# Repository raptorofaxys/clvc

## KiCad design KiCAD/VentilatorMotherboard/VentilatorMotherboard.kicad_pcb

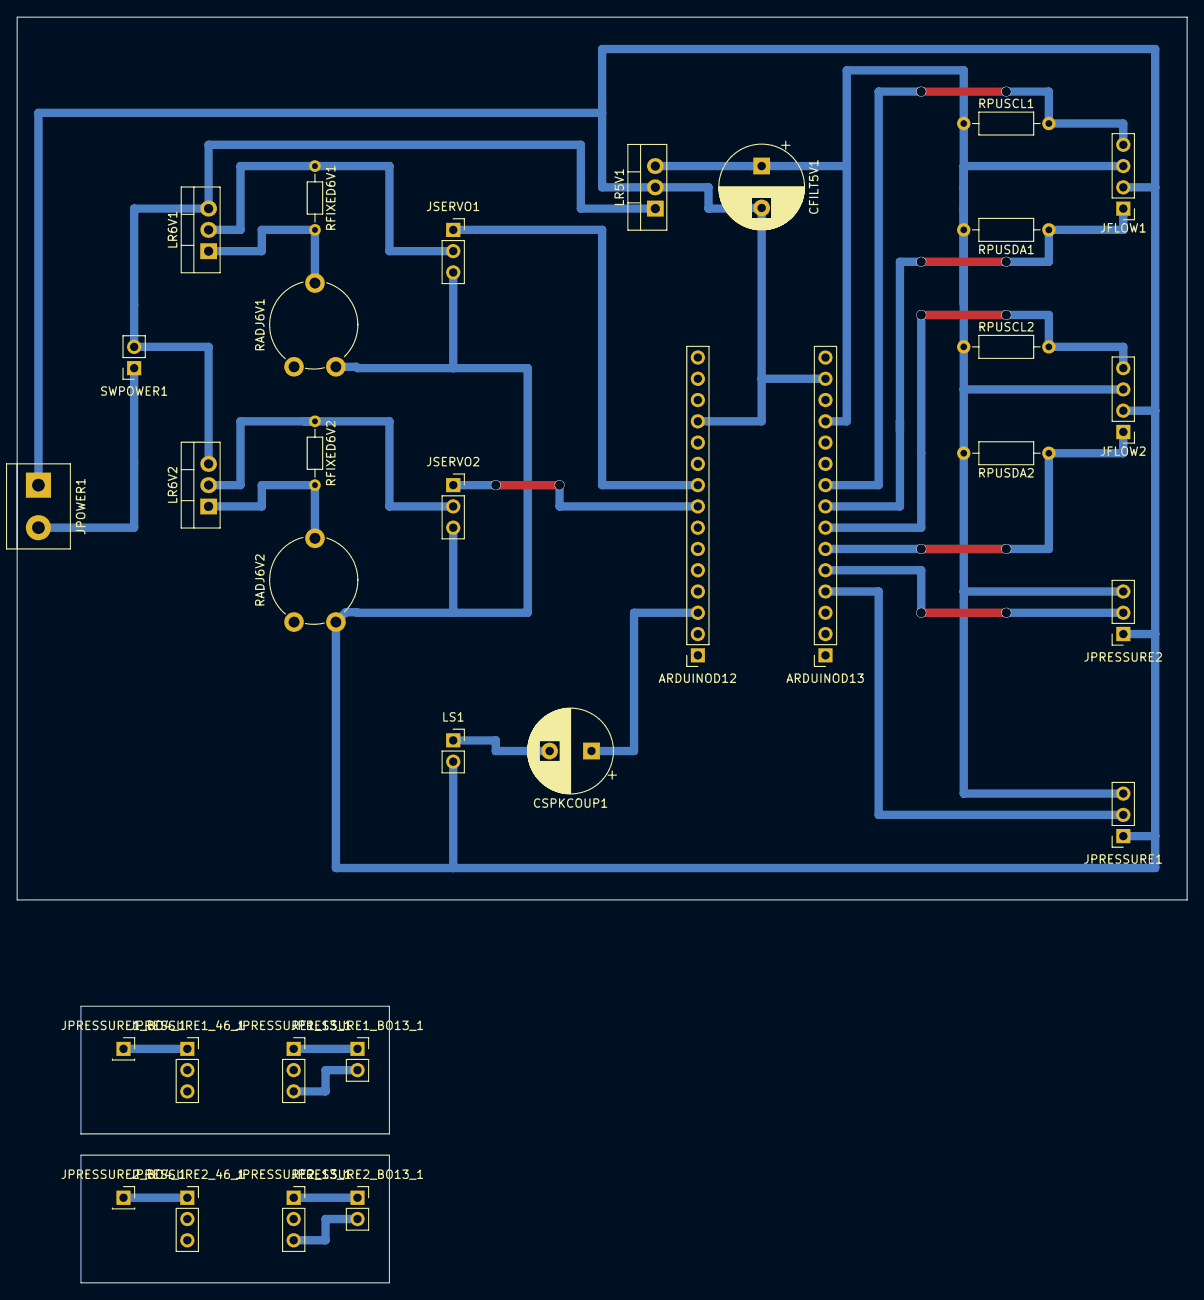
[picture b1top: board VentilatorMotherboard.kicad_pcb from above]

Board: 2 copper layers, 139.7 x 151.1 mm, 32 parts (0 on the bottom side), 24 nets.

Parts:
ARDUINOD12, ARDUINOD13: Conn_01x15_Female; PinSocket_1x15_P2.54mm_Vertical
CFILT5V1: 2200u; CP_Radial_D10.0mm_P5.00mm
CSPKCOUP1: 220u; CP_Radial_D10.0mm_P5.00mm
JFLOW1, JFLOW2: Conn_01x04_Male; PinHeader_1x04_P2.54mm_Vertical
JPOWER1: Conn_01x02_Female; TerminalBlock_bornier-2_P5.08mm
JPRESSURE1, JPRESSURE1_13_1, JPRESSURE1_46_1, JPRESSURE2, JPRESSURE2_13_1, JPRESSURE2_46_1: Conn_01x03_Male; PinSocket_1x03_P2.54mm_Vertical
JPRESSURE1_BO4_1, JPRESSURE2_BO4_1: Conn_01x01_Male; PinSocket_1x01_P2.54mm_Vertical
JPRESSURE1_BO13_1, JPRESSURE2_BO13_1: Conn_01x02_Male; PinSocket_1x02_P2.54mm_Vertical
JSERVO1, JSERVO2: Conn_01x03_Male; PinSocket_1x03_P2.54mm_Vertical
LR5V1: L7805; TO-220-3_Vertical
LR6V1, LR6V2: LM317_3PinPackage; TO-220-3_Vertical
LS1: Speaker; PinSocket_1x02_P2.54mm_Vertical
RADJ6V1, RADJ6V2: R_POT_TRIM; Potentiometer_Piher_PT-10-V10_Vertical
RFIXED6V1, RFIXED6V2: 220; R_Axial_DIN0204_L3.6mm_D1.6mm_P7.62mm_Horizontal
RPUSCL1, RPUSCL2: 4K7; R_Axial_DIN0207_L6.3mm_D2.5mm_P10.16mm_Horizontal
RPUSDA1, RPUSDA2: 4K7; R_Axial_DIN0207_L6.3mm_D2.5mm_P10.16mm_Horizontal
SWPOWER1: SW_SPST; PinSocket_1x02_P2.54mm_Vertical

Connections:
+5V: ARDUINOD13.12, CFILT5V1.1, JFLOW1.3, JFLOW2.3, JPRESSURE1.3, JPRESSURE2.3, LR5V1.3, RPUSCL1.1, RPUSCL2.1, RPUSDA1.2, RPUSDA2.2
/6V1: JSERVO1.2, LR6V1.2, RFIXED6V1.1
/6V2: JSERVO2.2, LR6V2.2, RFIXED6V2.1
/A0: ARDUINOD13.4, JPRESSURE1.2
/A1: ARDUINOD13.5, JPRESSURE2.2
/A2: ARDUINOD13.6, JFLOW2.1, RPUSDA2.1
/A3: ARDUINOD13.7, JFLOW2.4, RPUSCL2.2
/A4: ARDUINOD13.8, JFLOW1.1, RPUSDA1.1
/A5: ARDUINOD13.9, JFLOW1.4, RPUSCL1.2
/D4: ARDUINOD12.9, JSERVO1.1
/D5: ARDUINOD12.8, JSERVO2.1
/D10: ARDUINOD12.3, CSPKCOUP1.1
GND: ARDUINOD12.12, ARDUINOD13.14, CFILT5V1.2, JFLOW1.2, JFLOW2.2, JPOWER1.1, JPRESSURE1.1, JPRESSURE2.1, JSERVO1.3, JSERVO2.3, LR5V1.2, LS1.2, RADJ6V1.1, RADJ6V2.1
unnamed: CSPKCOUP1.2, LS1.1
unnamed: JPOWER1.2, SWPOWER1.1
unnamed: JPRESSURE1_13_1.1, JPRESSURE1_BO13_1.1
unnamed: JPRESSURE1_13_1.3, JPRESSURE1_BO13_1.2
unnamed: JPRESSURE1_46_1.1, JPRESSURE1_BO4_1.1
unnamed: JPRESSURE2_13_1.1, JPRESSURE2_BO13_1.1
unnamed: JPRESSURE2_13_1.3, JPRESSURE2_BO13_1.2
unnamed: JPRESSURE2_46_1.1, JPRESSURE2_BO4_1.1
unnamed: LR5V1.1, LR6V1.3, LR6V2.3, SWPOWER1.2
unnamed: LR6V1.1, RADJ6V1.2, RFIXED6V1.2
unnamed: LR6V2.1, RADJ6V2.2, RFIXED6V2.2

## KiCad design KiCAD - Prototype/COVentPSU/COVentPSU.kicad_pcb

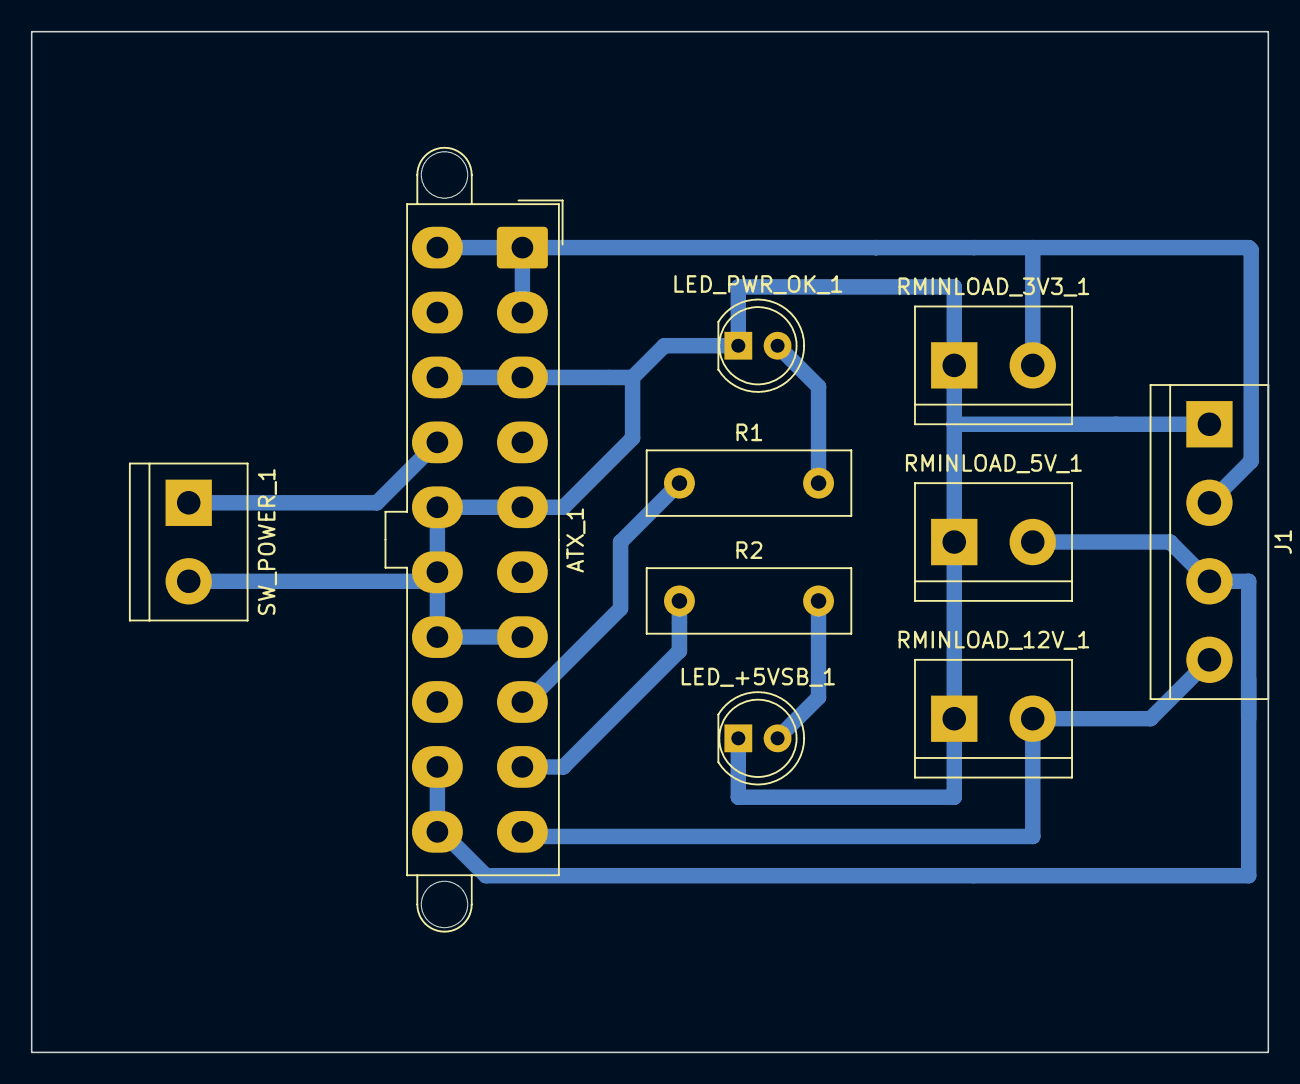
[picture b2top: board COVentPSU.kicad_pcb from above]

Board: 2 copper layers, 80.0 x 66.0 mm, 10 parts (0 on the bottom side), 9 nets.

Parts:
ATX_1: Conn_02x10_Top_Bottom; Molex_Mini-Fit_Jr_5566-20A2_2x10_P4.20mm_Vertical
J1: Conn_01x04_Female; TerminalBlock_bornier-4_P5.08mm
LED_+5VSB_1: LED_+5VSB; LED_D5.0mm
LED_PWR_OK_1: LED_PWR_OK; LED_D5.0mm
R1, R2: 300; R_Box_L13.0mm_W4.0mm_P9.00mm
RMINLOAD_3V3_1: 5; TerminalBlock_bornier-2_P5.08mm
RMINLOAD_5V_1, RMINLOAD_12V_1: 10; TerminalBlock_bornier-2_P5.08mm
SW_POWER_1: SW_POWER; TerminalBlock_bornier-2_P5.08mm

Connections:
+3V3: ATX_1.1, ATX_1.2, ATX_1.11, J1.2, RMINLOAD_3V3_1.2
+5V: ATX_1.19, ATX_1.20, J1.3, RMINLOAD_5V_1.2
+12V: ATX_1.10, J1.4, RMINLOAD_12V_1.2
/+5VSB: ATX_1.9, R2.1
/PWR_OK: ATX_1.8, R1.1
/PWR_ON: ATX_1.14, SW_POWER_1.1
GND: ATX_1.3, ATX_1.5, ATX_1.7, ATX_1.13, ATX_1.15, ATX_1.16, ATX_1.17, J1.1, LED_+5VSB_1.1, LED_PWR_OK_1.1, RMINLOAD_3V3_1.1, RMINLOAD_5V_1.1, RMINLOAD_12V_1.1, SW_POWER_1.2
unnamed: LED_+5VSB_1.2, R2.2
unnamed: LED_PWR_OK_1.2, R1.2

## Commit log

2020-03-27 Initial commit
    Interfaced:
    -speaker
    -servos
    -pressure sensors
    -hardware I2C flowmeter
2020-03-28 All sensors integrated
    Make the default number of float decimals configurable .
    Add PrintStringHex32.
    Flow sensor only reads when more than 1ms has elapsed.
    Flow sensor checks that device is reachable at start.
    Add humidity and temperature sensor logic.
    Make sensors and actuators individually toggleable at compilation level for debugging.
2020-03-29 Blink LED on D13 when a halt/assert occurs for easier debugging without a PC
2020-03-29 Add a temporary Arduino sketch we can use as a scratchpad to debug remotely
2020-03-29 Add motherboard KiCAD
    (also, rename a bunch of stuff to avoid naming conflicts)
2020-03-29 Rename some directories to avoid naming conflicts
2020-03-29 Rename more files and make the playground sketch center the servos
2020-03-29 gitignore and editorconfig for Processing
2020-03-29 UI framework
2020-03-29 Nuked everything. Display placeholder UI.
2020-03-29 Zero the servos at one end of the range
2020-03-29 Adjust the servo sweeping motion in the playground
2020-03-29 UIElementRT for writing to a render target, Converted UIGraph to UIElementRT
2020-03-29 Font & Text placeholders
2020-03-29 Remove serial print from playground
2020-03-29 Arduino can send hashed structured messages to Processing
2020-03-29 Fixed graph running fade; Added graph circle on current value
2020-03-29 Rename OutputState to MachineState for clarity
2020-03-29 Processing can now send hash-verified messages to the Arduino
2020-03-29 Integrate serial communication example into main Processing sketch
2020-03-30 OnResize event at UIElement level; UIGraph colors, origin line, range; New fonts
2020-03-30 Changed layout to include InfoPanel
2020-03-30 Update serial transmission structures to reflect our latest UX map
2020-03-30 Smoothen all the things!
2020-03-30 UIGraph now has a public SetValue
    -Nicer fake graph values
    -Explicit frame rate
    -Resolution closer to target device size
    -Smooth = true
2020-03-30 UIText & UIOverlappingGroup
2020-03-30 Add low-pass filtering logic
2020-03-30 If the graph advances without having a new sample, hold the previous value
2020-03-30 Read and graph values from the microcontroller
2020-03-30 Add extremely crude transfer synchronization between MCU and PC
2020-03-30 Tracking message send/receive rates and reporting them to the UI
    Also:
    Add the basis for virtual sensors inputs.
2020-03-30 WIP trigger logic and error condition tracking
2020-03-30 UI can send punctual events to MCU
2020-03-30 Compute breath phases for timed and manual trigger logic; add UI state validation logic
2020-03-30 Reduce the servo signal timing bounds a little to try to avoid an end-stick
2020-03-30 Make playground swing servos and display sensor state
2020-03-30 Correct servo swinging logic in playground
2020-03-30 Switch pressure units to cmH2O
2020-03-31 Add virtual pressure-controlled mode along with basic pressure virtual input simulation
    Add debug floats in machine state to help with debugging
2020-03-31 InfoPanel & UIInfoText for displaying label and float value
    Renamed global variables to camelCase
2020-03-31 UIControlButton
2020-03-31 Inspiration Time control; Higher-res font
2020-03-31 Mask target changes from error rate calculations to help stabilize controller; send updates every frame to prevent very strange behaviour that will no doubt become clear the moment I step away from t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
2020-03-31 Track peak pressure; display values from MCU on UI
2020-03-31 Track and display plateau pressure and PEEP
2020-03-31 Display inspiration time
2020-03-31 Enable use of COM3 for SIMOROBO
2020-03-31 Report breaths per minute and I:E ratio to UI
2020-03-31 FloatToRoundedString
2020-03-31 More samples on graph; appDebug to control verbose
2020-03-31 UIMenuButton
2020-03-31 UIInteractiveElement, UIRadioButton, UITrackBar
2020-03-31 Send values from UI to Arduino
2020-03-31 Trackbar trigger only on click unless touch screen
2020-03-31 FiO2 conversion 01 to %
2020-03-31 Insp Time display decimal and range tweak
2020-03-31 Restored resolution
2020-03-31 Improve software limits
    Made static limits the same in Processing and on the MCU.
    Compute dynamic PEEP and inspiratory time limits on the MCU.
2020-03-31 Track sensed PEEP across rest as well and lower minimum I:E ratio to 1.0
    Might get rid of the rest phase in the long run.
2020-03-31 Make COM port name data-driven
2020-03-31 Inspiratory pressure stacks on top of the PEEP
2020-03-31 Prevent NaNs in pressure trackers
2020-03-31 Strip unused UI state data
2020-03-31 The controller can now correct the inspiratory time on the UI side when it gets clamped because of breath rate settings
2020-03-31 Graph bgcolor
2020-03-31 Refactor pressure tracking code as a step towards plateau tracking
2020-03-31 Color the background of the pressure graph as a function of the breath phase
2020-03-31 Graph minor clean up of background color
2020-03-31 Properly track inspiration plateau and peep plateau
2020-03-31 Make virtual lung inflate/deflate to model flow
2020-03-31 Make total system flow graph work
2020-03-31 Compute and display tidal volumes
2020-03-31 Add total volume computation as well as minute ventilation
2020-03-31 Refine the lung model slightly
2020-03-31 Relative trackbar
2020-03-31 OnRollOut event
2020-04-01 Visual feedback on selection of Control Buttons
2020-04-01 Final firmware we ran the tests with
2020-04-01 Fix for touch screen PC
2020-04-01 Fixed Graph skips
    - Bumped strokeWeight to 1.5, issue was apparently line rasterizer
    - Converted every part of the calculation to float
2020-04-02 Graph background improvements
    -Graph marks on axis at every second
    -Graph background is fully drawn on init
    -Graph sample count matches 12 seconds of graph
    -Resolution 960x600, half of target screen
2020-04-02 Font resize and adjustments
    -Font size auto-scales with window height
    -Adjusted font size of several UITexts
2020-04-05 TrackBar visuals
2020-04-05 A place for DrawFunctions that can't be made static
2020-04-06 Add power switch to PCB; add some text annotations
2020-04-06 Final submission docs etc.
2020-04-06 Minor cleanup before submission
2020-04-06 Re-enable virtual inputs by default and change some constants to make the simulation behave a little more like the observed physical system
2020-04-06 Initialize everything just to be sure - that _totalSeconds float in the pressure sensor for virtual input logic could likely have randomly caused NaNs
2020-04-07 Padding first pass
2020-04-09 Minor visual tweaks
2020-04-09 App and UIFont classes
    Also some UIGraph visual tweaks
2020-04-10 Padding now scales with resolution
2020-04-10 UIGraph2
